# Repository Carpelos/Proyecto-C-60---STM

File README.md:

# Proyecto-C-60-STM
 60% keyboard with southpaw numpad

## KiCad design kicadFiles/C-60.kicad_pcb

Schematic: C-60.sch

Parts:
C1, C2, C3, C4, C5, C6, C7, C8, C9, C10, C11, C12, C13, C14, C15, C16, C17, C18: 0.1uf; C_0805_2012Metric_Pad1.15x1.40mm_HandSolder
CB1, CB2, CB3, CB4: 100n; C_0805_2012Metric_Pad1.15x1.40mm_HandSolder
CB5: 10u; C_0805_2012Metric_Pad1.15x1.40mm_HandSolder
CF1: 10u; C_0805_2012Metric_Pad1.15x1.40mm_HandSolder
CRO1: 100n; C_0805_2012Metric_Pad1.15x1.40mm_HandSolder
CRST1: 10u; C_0805_2012Metric_Pad1.15x1.40mm_HandSolder
CRST2: 4.7n; C_0805_2012Metric_Pad1.15x1.40mm_HandSolder
CSH1: 4.7n; C_0805_2012Metric_Pad1.15x1.40mm_HandSolder
CUSB1: 4.7n; C_0805_2012Metric_Pad1.15x1.40mm_HandSolder
D1, D2, D20, D21, D22, D23, D24, D25, D26, D27, D28, D29, D30, D31, D32, D33, D34, D37, D38, D39, D40, D41, D42, D43, D44, D45, D46, D47, D48, D49, D50, D51, D52, D53, D55, D56, D57, D59, D61, D62, D63, D64, D65, D66, D67, D68, D69, D70, D71, D72, D73, D75, D76, D77, D79, D80, D81, D82, D83, D84, D85, D86, D87, D88, D89, D90, D92, D93, D94, D95, D96, D97, D98, D99, D100, D101, D102, D103, D106, D107, D108: 1N4148; D_SOD-123
D3, D4, D5, D6, D7, D8, D9, D10, D11, D12, D13, D14, D15, D16, D17, D18, D19, D35: WS2812B; LED_WS2812B_PLCC4_5.0x5.0mm_P3.2mm
DF1: RB060M-60TR; D_SOD-123
DRST1: 1N4148; D_SOD-123
DS33: 1N4007; D_SOD-123
F1: 1.5A trip polyfuse; Fuse_1206_3216Metric_Pad1.42x1.75mm_HandSolder
J1: TYPE-C-31-M12_13; TYPE-C-31-M-12
J5: Conn_ARM_JTAG_SWD_10; PinHeader_2x05_P2.54mm_Vertical
LEDCAPS1: LED; LED_THT_2.54mm
LEDNUM1: LED; LED_THT_2.54mm
LEDSCRL1: LED; LED_THT_2.54mm
QRST1: DTC123J; SOT-23
R1: 330; R_0805_2012Metric_Pad1.15x1.40mm_HandSolder
RCC1, RCC2: 5.1k; R_0805_2012Metric_Pad1.15x1.40mm_HandSolder
RF1: 100k; R_0805_2012Metric_Pad1.15x1.40mm_HandSolder
RI1, RI2, RI3: 360; R_0805_2012Metric_Pad1.15x1.40mm_HandSolder
RRST1: 100k; R_0805_2012Metric_Pad1.15x1.40mm_HandSolder
RSH1: 1M; R_0805_2012Metric_Pad1.15x1.40mm_HandSolder
SW1: Split 0L; MX100
SW2: Split 0R; MX100
SW3: SHIFT; MX275
SW4: Code; MX100
SW20: `; MX100
SW21, SW92: 1; MX100
SW22, SW93: 2; MX100
SW23, SW94: 3; MX100
SW24, SW75: 4; MX100
SW25, SW76: 5; MX100
SW26, SW77: 6; MX100
SW27, SW55: 7; MX100
SW28, SW56: 8; MX100
SW29, SW57: 9; MX100
SW30: 0; MX100
SW31: -; MX100
SW32: =; MX100
SW33: Backspace; MX200
SW37: NumLock; MX100
SW38: p/; MX100
SW39: p*; MX100
SW40: Tab; MX150
SW41: Q; MX100
SW42: W; MX100
SW43: E; MX100
SW44: R; MX100
SW45: T; MX100
SW46: Y; MX100
SW47: U; MX100
SW48: I; MX100
SW49: O; MX100
SW50: P; MX100
SW51: [{; MX100
SW52: ]}; MX100
SW53: \\|; MX150
SW58: ANSI LShift; MX225
SW59: MXSwitch; MX200V
SW60: CAPS; MX175
SW61: StCAPS; MX125
SW62: A; MX100
SW63: S; MX100
SW64: D; MX100
SW65: F; MX100
SW66: G; MX100
SW67: H; MX100
SW68: J; MX100
SW69: K; MX100
SW70: L; MX100
SW71: ;:; MX100
SW72: \"; MX100
SW73: ENTER; MX225
SW78: ISO Slash; MX100
SW79: ISO LShift; MX125
SW80: Z; MX100
SW81: X; MX100
SW82: C; MX100
SW83: V; MX100
SW84: B; MX100
SW85: N; MX100
SW86: M; MX100
SW87: ,<; MX100
SW88: .>; MX100
SW89: /?; MX100
SW90: SHIFT; MX175
SW95: Pent; MX200V
SW96: RCTL; MX125
SW97, SW101: RWIN; MX125
SW98: LALT; MX125
SW99: SPACE; MX625R
SW100: RALT; MX125
SW102: MENU; MX125
SW103: RCTRL; MX125
SW106: P0; MX200R
SW107: P.Del; MX100
SW108: p-; MX100
SW113: ISO Enter; MX_ISOEnter
SW114: ISO tilde; MX100
SWRST1: SW_Push; smdPushBtn
U1: STM32F072_LQFP48; LQFP-48_7x7mm_P0.5mm
U2: TLV1117-33; SOT-223-3_TabPin2
U3: USBLC6-2SC6; SOT-23-6

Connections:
3.3V: CB1.1, CB2.1, CB3.1, CB4.1, CB5.1, CRO1.2, DS33.2 (A), J5.1 (VTref), SWRST1.1, U1.1 (VBAT), U1.9 (VDDA), U1.24 (VDD), U1.36 (VDDIO2), U1.48 (VDD), U2.2 (VO)
5V: C1.1, C2.1, C3.1, C4.1, C5.1, C6.1, C7.1, C8.1, C9.1, C10.1, C11.1, C12.1, C13.1, C14.1, C15.1, C16.1, C17.1, C18.1, CF1.2, D3.1 (VDD), D4.1 (VDD), D5.1 (VDD), D6.1 (VDD), D7.1 (VDD), D8.1 (VDD), D9.1 (VDD), D10.1 (VDD), D11.1 (VDD), D12.1 (VDD), D13.1 (VDD), D14.1 (VDD), D15.1 (VDD), D16.1 (VDD), D17.1 (VDD), D18.1 (VDD), D19.1 (VDD), D35.1 (VDD), DF1.1 (K), DS33.1 (K), F1.1, RF1.1, U2.3 (VI)
BOOT0: CRST1.2, DRST1.1 (K), RRST1.1, U1.44 (BOOT0)
Col1: SW59.1 (Col), SW95.1 (Col), SW108.1 (Col), U1.21 (SPI2_CK/I2C2_SCL/TIM2_CH3/PB10)
Col2: SW39.1 (Col), SW57.1 (Col), SW77.1 (Col), SW94.1 (Col), SW107.1 (Col), U1.22 (I2C2_SDA/TIM2_CH4/EVENTOUT/PB11)
Col3: SW1.1 (Col), SW38.1 (Col), SW56.1 (Col), SW76.1 (Col), SW93.1 (Col), SW106.1 (Col), U1.25 (EVENTOUT/PB12)
Col4: SW2.1 (Col), SW37.1 (Col), SW55.1 (Col), SW75.1 (Col), SW92.1 (Col), U1.26 (SPI2_SCK/I2S2_CK/I2C2_SCL/PB13)
Col5: SW20.1 (Col), SW40.1 (Col), SW58.1 (Col), SW60.1 (Col), SW61.1 (Col), SW79.1 (Col), SW96.1 (Col), U1.10 (ADCIN2/PA0)
Col6: SW21.1 (Col), SW41.1 (Col), SW62.1 (Col), SW78.1 (Col), SW97.1 (Col), U1.11 (ADCIN1/PA1)
Col7: SW22.1 (Col), SW42.1 (Col), SW63.1 (Col), SW80.1 (Col), SW98.1 (Col), U1.12 (TIM2_CH3/ADCIN2/WKUP4/PA2)
Col8: SW23.1 (Col), SW43.1 (Col), SW64.1 (Col), SW81.1 (Col), U1.31 (TIM1_CH3/PA10)
Col9: SW24.1 (Col), SW44.1 (Col), SW65.1 (Col), SW82.1 (Col), U1.38 (PA15)
Col10: SW25.1 (Col), SW45.1 (Col), SW66.1 (Col), SW83.1 (Col), U1.39 (SPI1_SCK/I2S1CK/PB3)
Col11: SW26.1 (Col), SW46.1 (Col), SW67.1 (Col), SW84.1 (Col), SW99.1 (Col), U1.40 (SPI1_MISO_I2S1MCK/PB4)
Col12: SW27.1 (Col), SW47.1 (Col), SW68.1 (Col), SW85.1 (Col), U1.41 (TIM3_CH2/SPI1_MOSI/I2S1_SD/I2C1_SMBA/PB5)
Col13: SW28.1 (Col), SW48.1 (Col), SW69.1 (Col), SW86.1 (Col), U1.45 (I2C1SCL/PB8)
Col14: SW29.1 (Col), SW49.1 (Col), SW70.1 (Col), SW87.1 (Col), U1.46 (SPI1_NSS/I2S2_WS/I2C1_SDA/PB9)
Col15: SW30.1 (Col), SW50.1 (Col), SW71.1 (Col), SW88.1 (Col), SW100.1 (Col), U1.2 (PC13/WKUP2)
Col16: SW31.1 (Col), SW51.1 (Col), SW72.1 (Col), SW89.1 (Col), SW101.1 (Col), U1.6 (PF1/OscOut)
Col17: SW3.1 (Col), SW32.1 (Col), SW52.1 (Col), SW73.1 (Col), SW90.1 (Col), SW102.1 (Col), SW114.1 (Col), U1.4 (PC15/Osc32Out)
Col18: SW4.1 (Col), SW33.1 (Col), SW53.1 (Col), SW103.1 (Col), SW113.1 (Col), U1.3 (PC14/Osc32In)
D+: U1.33 (PA12/TIM1_ETR/EVENTOUT/USB_DP), U3.4 (IO2)
D-: U1.32 (PA11/TIM1CH4/EVENTOUT/USB_DM), U3.6 (IO1)
DBus+: J1.A6 (D+), J1.B6 (D+), U3.3 (IO2)
DBus-: J1.A7 (D-), J1.B7 (D-), U3.1 (IO1)
GND: C1.2, C2.2, C3.2, C4.2, C5.2, C6.2, C7.2, C8.2, C9.2, C10.2, C11.2, C12.2, C13.2, C14.2, C15.2, C16.2, C17.2, C18.2, CB1.2, CB2.2, CB3.2, CB4.2, CB5.2, CF1.1, CRO1.1, CRST1.1, CRST2.2, CSH1.1, CUSB1.1, D3.3 (VSS), D4.3 (VSS), D5.3 (VSS), D6.3 (VSS), D7.3 (VSS), D8.3 (VSS), D9.3 (VSS), D10.3 (VSS), D11.3 (VSS), D12.3 (VSS), D13.3 (VSS), D14.3 (VSS), D15.3 (VSS), D16.3 (VSS), D17.3 (VSS), D18.3 (VSS), D19.3 (VSS), D35.3 (VSS), DF1.2 (A), J1.A1 (GND), J1.B1 (GND), J5.3 (GND), J5.5 (GND), J5.9 (GNDDetect), LEDCAPS1.K, LEDNUM1.K, LEDSCRL1.K, QRST1.2 (E), RCC1.1, RCC2.1, RF1.2, RRST1.2, RSH1.2, U1.8 (VSSA), U1.23 (VSS), U1.35 (VSS), U1.47 (VSS), U2.1 (GND), U3.2 (GND)
INDICATOR1: RI1.1, U1.28 (SPI2_MOSI/I2S2_SD/PB15)
INDICATOR2: RI2.1, U1.29 (TIM1_CH1/EVENTOUT/MCO/PA8)
INDICATOR3: RI3.1, U1.30 (TIM1_CH2/PA9)
LED_RGB: R1.1, U1.16 (SPI1_MISO/I2S1_MCK/TIM3_CH1/ADCIN6/PA6)
NRST: CRST2.1, J5.10 (~RESET~), QRST1.3 (C), U1.7 (NRST)
unnamed: CSH1.2, J1.S (SHIELD), RSH1.1
unnamed: D1.2 (A), SW2.2 (Row)
unnamed: D2.2 (A), SW4.2 (Row)
unnamed: D3.2 (DOUT), D4.4 (DIN)
unnamed: D3.4 (DIN), R1.2
unnamed: D4.2 (DOUT), D5.4 (DIN)
unnamed: D5.2 (DOUT), D6.4 (DIN)
unnamed: D6.2 (DOUT), D7.4 (DIN)
unnamed: D7.2 (DOUT), D8.4 (DIN)
unnamed: D8.2 (DOUT), D9.4 (DIN)
unnamed: D10.2 (DOUT), D11.4 (DIN)
unnamed: D9.2 (DOUT), D10.4 (DIN)
unnamed: D11.2 (DOUT), D12.4 (DIN)
unnamed: D12.2 (DOUT), D13.4 (DIN)
unnamed: D13.2 (DOUT), D14.4 (DIN)
unnamed: D14.2 (DOUT), D15.4 (DIN)
unnamed: D15.2 (DOUT), D16.4 (DIN)
unnamed: D16.2 (DOUT), D17.4 (DIN)
unnamed: D17.2 (DOUT), D18.4 (DIN)
unnamed: D18.2 (DOUT), D19.4 (DIN)
unnamed: D19.2 (DOUT), D35.4 (DIN)
unnamed: D20.2 (A), SW20.2 (Row)
unnamed: D21.2 (A), SW21.2 (Row)
unnamed: D22.2 (A), SW22.2 (Row)
unnamed: D23.2 (A), SW23.2 (Row)
unnamed: D24.2 (A), SW24.2 (Row)
unnamed: D25.2 (A), SW25.2 (Row)
unnamed: D26.2 (A), SW26.2 (Row)
unnamed: D27.2 (A), SW27.2 (Row)
unnamed: D28.2 (A), SW28.2 (Row)
unnamed: D29.2 (A), SW29.2 (Row)
unnamed: D30.2 (A), SW30.2 (Row)
unnamed: D31.2 (A), SW31.2 (Row)
unnamed: D32.2 (A), SW32.2 (Row)
unnamed: D33.2 (A), SW33.2 (Row)
unnamed: D34.2 (A), SW78.2 (Row)
unnamed: D37.2 (A), SW37.2 (Row)
unnamed: D38.2 (A), SW38.2 (Row)
unnamed: D39.2 (A), SW39.2 (Row)
unnamed: D40.2 (A), SW40.2 (Row)
unnamed: D41.2 (A), SW41.2 (Row)
unnamed: D42.2 (A), SW42.2 (Row)
unnamed: D43.2 (A), SW43.2 (Row)
unnamed: D44.2 (A), SW44.2 (Row)
unnamed: D45.2 (A), SW45.2 (Row)
unnamed: D46.2 (A), SW46.2 (Row)
unnamed: D47.2 (A), SW47.2 (Row)
unnamed: D48.2 (A), SW48.2 (Row)
unnamed: D49.2 (A), SW49.2 (Row)
unnamed: D50.2 (A), SW50.2 (Row)
unnamed: D51.2 (A), SW51.2 (Row)
unnamed: D52.2 (A), SW52.2 (Row)
unnamed: D53.2 (A), SW53.2 (Row), SW113.2 (Row)
unnamed: D55.2 (A), SW55.2 (Row)
unnamed: D56.2 (A), SW56.2 (Row)
unnamed: D57.2 (A), SW57.2 (Row)
unnamed: D59.2 (A), SW59.2 (Row)
unnamed: D61.2 (A), SW60.2 (Row), SW61.2 (Row)
unnamed: D62.2 (A), SW62.2 (Row)
unnamed: D63.2 (A), SW63.2 (Row)
unnamed: D64.2 (A), SW64.2 (Row)
unnamed: D65.2 (A), SW65.2 (Row)
unnamed: D66.2 (A), SW66.2 (Row)
unnamed: D67.2 (A), SW67.2 (Row)
unnamed: D68.2 (A), SW68.2 (Row)
unnamed: D69.2 (A), SW69.2 (Row)
unnamed: D70.2 (A), SW70.2 (Row)
unnamed: D71.2 (A), SW71.2 (Row)
unnamed: D72.2 (A), SW72.2 (Row)
unnamed: D73.2 (A), SW73.2 (Row), SW114.2 (Row)
unnamed: D75.2 (A), SW75.2 (Row)
unnamed: D76.2 (A), SW76.2 (Row)
unnamed: D77.2 (A), SW77.2 (Row)
unnamed: D79.2 (A), SW58.2 (Row), SW79.2 (Row)
unnamed: D80.2 (A), SW80.2 (Row)
unnamed: D81.2 (A), SW81.2 (Row)
unnamed: D82.2 (A), SW82.2 (Row)
unnamed: D83.2 (A), SW83.2 (Row)
unnamed: D84.2 (A), SW84.2 (Row)
unnamed: D85.2 (A), SW85.2 (Row)
unnamed: D86.2 (A), SW86.2 (Row)
unnamed: D87.2 (A), SW87.2 (Row)
unnamed: D88.2 (A), SW88.2 (Row)
unnamed: D89.2 (A), SW89.2 (Row)
unnamed: D90.2 (A), SW3.2 (Row), SW90.2 (Row)
unnamed: D92.2 (A), SW92.2 (Row)
unnamed: D93.2 (A), SW93.2 (Row)
unnamed: D94.2 (A), SW94.2 (Row)
unnamed: D95.2 (A), SW95.2 (Row)
unnamed: D96.2 (A), SW96.2 (Row)
unnamed: D97.2 (A), SW97.2 (Row)
unnamed: D98.2 (A), SW98.2 (Row)
unnamed: D99.2 (A), SW99.2 (Row)
unnamed: D100.2 (A), SW100.2 (Row)
unnamed: D101.2 (A), SW101.2 (Row)
unnamed: D102.2 (A), SW102.2 (Row)
unnamed: D103.2 (A), SW103.2 (Row)
unnamed: D106.2 (A), SW1.2 (Row), SW106.2 (Row)
unnamed: D107.2 (A), SW107.2 (Row)
unnamed: D108.2 (A), SW108.2 (Row)
unnamed: DRST1.2 (A), QRST1.1 (B), SWRST1.2
unnamed: J1.A5 (CC1), RCC1.2
unnamed: J1.B5 (CC2), RCC2.2
unnamed: LEDCAPS1.A, RI3.2
unnamed: LEDNUM1.A, RI2.2
unnamed: LEDSCRL1.A, RI1.2
Row1: D20.1 (K), D21.1 (K), D22.1 (K), D23.1 (K), D24.1 (K), D25.1 (K), D26.1 (K), D27.1 (K), D28.1 (K), D29.1 (K), D30.1 (K), D31.1 (K), D32.1 (K), D33.1 (K), D37.1 (K), D38.1 (K), D39.1 (K), D108.1 (K), U1.27 (SPI2_MISO/I2S2_MCK/I2C2_SDA/PB14)
Row2: D40.1 (K), D41.1 (K), D42.1 (K), D43.1 (K), D44.1 (K), D45.1 (K), D46.1 (K), D47.1 (K), D48.1 (K), D49.1 (K), D50.1 (K), D51.1 (K), D52.1 (K), D53.1 (K), D55.1 (K), D56.1 (K), D57.1 (K), U1.43 (I2C1_SDA/PB7)
Row3: D59.1 (K), D61.1 (K), D62.1 (K), D63.1 (K), D64.1 (K), D65.1 (K), D66.1 (K), D67.1 (K), D68.1 (K), D69.1 (K), D70.1 (K), D71.1 (K), D72.1 (K), D73.1 (K), D75.1 (K), D76.1 (K), D77.1 (K), U1.42 (I2C1SCL/PB6)
Row4: D2.1 (K), D34.1 (K), D79.1 (K), D80.1 (K), D81.1 (K), D82.1 (K), D83.1 (K), D84.1 (K), D85.1 (K), D86.1 (K), D87.1 (K), D88.1 (K), D89.1 (K), D90.1 (K), D92.1 (K), D93.1 (K), D94.1 (K), D95.1 (K), U1.18 (TIM3_CH3/ADCIN8/PB0)
Row5: D1.1 (K), D96.1 (K), D97.1 (K), D98.1 (K), D99.1 (K), D100.1 (K), D101.1 (K), D102.1 (K), D103.1 (K), D106.1 (K), D107.1 (K), U1.19 (TIM3_CH4/ADCIN9/PB1)
Row6: U1.20 (PB2)
SWCLK: J5.4 (SWDCLK/TCK), U1.37 (PA14/SWCLK)
SWDIO: J5.2 (SWDIO/TMS), U1.34 (PA13/USBNOE/SWDIO)
VBUS: CUSB1.2, F1.2, J1.A4 (VBUS), J1.B4 (VBUS), U3.5 (VBUS)

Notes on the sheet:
Hard reset circuit
Power supply and protection circuit
Shield net
Switch matrix
USB Connector
RGB UNDERGLOW
MCU
SWD
Data ESD Protection
Numlock
Tab
Caps
Enter
B1RCtrl
R1Alt
R1Win
P.Del
B2LCtrl
B2LWin
B1LAlt
B1Spc
Backspace
Shift
CBs for "Capacitors - Bypass"
DF for "Diode - Fuse"
DS33 for "Schottky Diode - 3.3V"
CRI for Capacitor - Regulator Input
CRO for Capacitor - Regulator Output
ISO Enter
Indicator lights
Bypass capacitors
Menu
Rctrl
ISO Tilde
Split 0L
Split 0R
Code

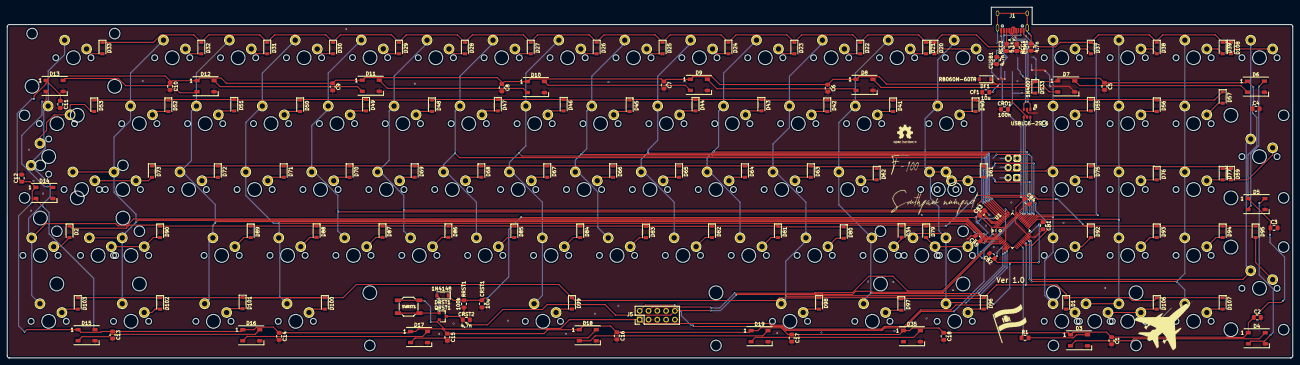
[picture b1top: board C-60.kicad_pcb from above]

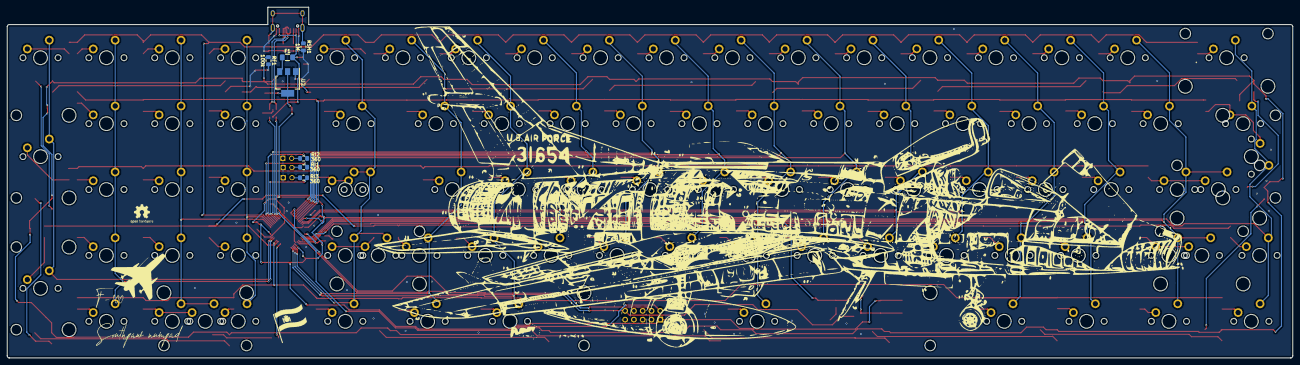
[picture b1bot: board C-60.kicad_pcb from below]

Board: 2 copper layers, 371.6 x 101.4 mm, 238 parts (7 on the bottom side), 145 nets.

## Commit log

2020-09-11 ver 1 firmware added
2020-09-19 updated acrilic case
